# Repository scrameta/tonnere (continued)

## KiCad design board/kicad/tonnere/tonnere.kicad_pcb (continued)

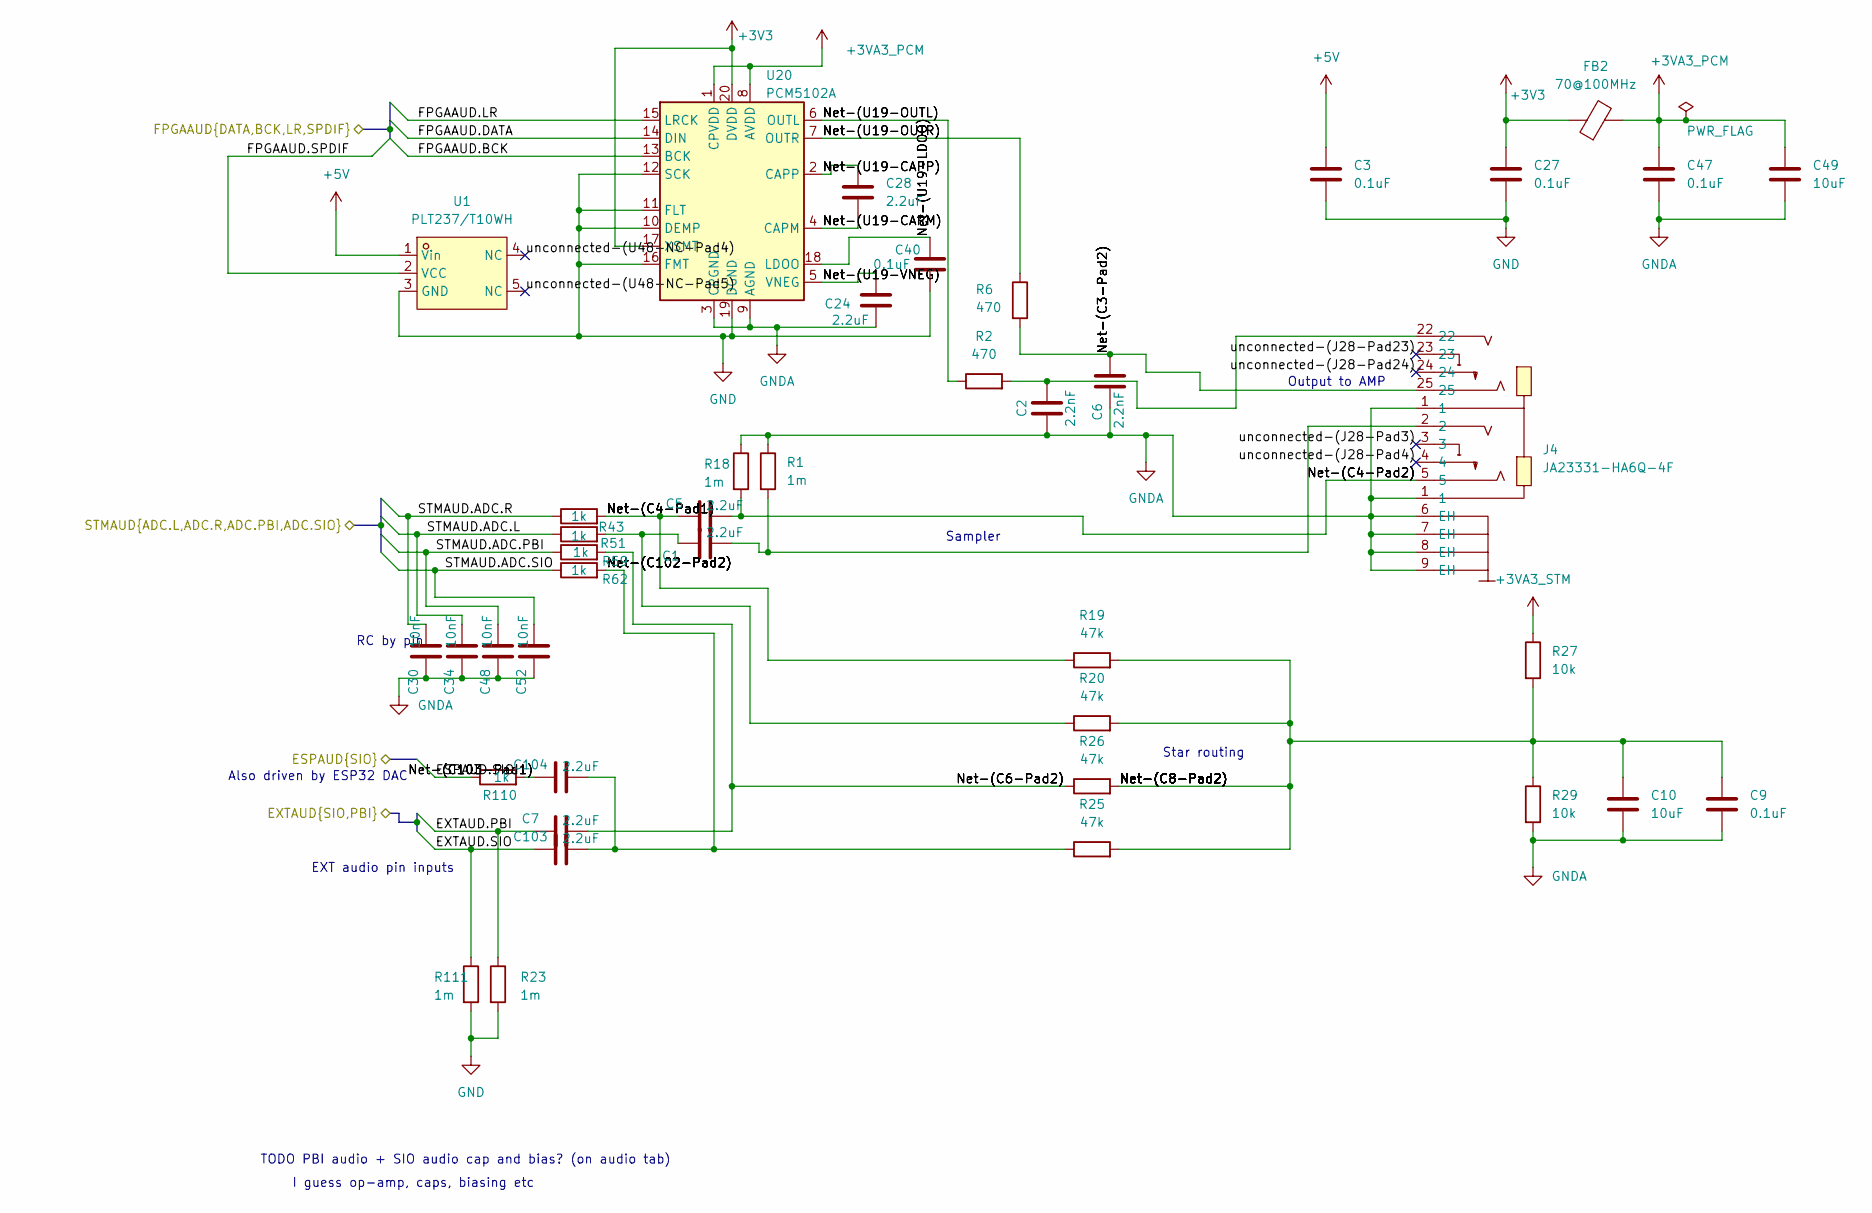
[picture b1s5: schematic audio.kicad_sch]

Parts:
C1, C5, C7, C24, C28, C103, C104: 2.2uF; C_0603_1608Metric; LCSC C23630
C2, C6: 2.2nF; C_0603_1608Metric; LCSC C1604
C3, C9, C27, C40, C47: 0.1uF; C_0603_1608Metric; LCSC C14663
C10, C49: 10uF; C_0805_2012Metric; LCSC C15850
C30, C34, C48, C52: 10nF; C_0603_1608Metric; LCSC C57112
FB2: 70@100MHz; L_0805_2012Metric; LCSC C1012
J4: JA23331-HA6Q-4F; AUDIO-TH_JA23331-HA6Q-4F; MPN JA23331-HA6Q-4F; LCSC Part C225739
R1, R18, R23, R111: 1m; R_0603_1608Metric; LCSC C22935
R2, R6: 470; R_0603_1608Metric; LCSC C23179
R19, R20, R25, R26: 47k; R_0603_1608Metric; LCSC C25819
R27, R29: 10k; R_0603_1608Metric; LCSC C25804
R43, R51, R59, R62, R110: 1k; R_0603_1608Metric; LCSC C21190
U1: PLT237/T10WH; CONN-TH_PLT237-T10WH; MPN PLT237/T10WH; LCSC Part C17296340
U20: PCM5102A; TSSOP-20_4.4x6.5mm_P0.65mm; LCSC C107671

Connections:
+3V3: C27.2, FB2.1, U20.17 (XSMT), U20.20 (DVDD); also elsewhere on the board
+3VA3_PCM: C47.2, C49.1, FB2.2, U20.1 (CPVDD), U20.8 (AVDD)
+3VA3_STM: R27.1; also elsewhere on the board
+5V: C3.2, U1.1 (Vin); also elsewhere on the board
/AtariInterfaces/EXTAUD.PBI: C7.1, R23.1; also elsewhere on the board
/AtariInterfaces/EXTAUD.SIO: C103.1, R111.1; also elsewhere on the board
/Audio/ESPAUD.SIO: R110.1; also elsewhere on the board
/Audio/FPGAAUD.BCK: U20.13 (BCK); also elsewhere on the board
/Audio/FPGAAUD.DATA: U20.14 (DIN); also elsewhere on the board
/Audio/FPGAAUD.LR: U20.15 (LRCK); also elsewhere on the board
/Audio/FPGAAUD.SPDIF: U1.2 (VCC); also elsewhere on the board
/Audio/Net-(C3-Pad2): C6.2, J4.25, R6.2
/Audio/Net-(C4-Pad1): C5.1, R19.1, R43.2
/Audio/Net-(C4-Pad2): C5.2, J4.5, R18.2
/Audio/Net-(C6-Pad2): C7.2, R26.1, R59.2
/Audio/Net-(C8-Pad2): C9.2, C10.2, R19.2, R20.2, R25.2, R26.2, R27.2, R29.1
/Audio/Net-(C102-Pad2): C103.2, C104.2, R25.1, R62.2
/Audio/Net-(C103-Pad1): C104.1, R110.2
/Audio/Net-(U19-CAPM): C28.1, U20.4 (CAPM)
/Audio/Net-(U19-CAPP): C28.2, U20.2 (CAPP)
/Audio/Net-(U19-LDOO): C40.2, U20.18 (LDOO)
/Audio/Net-(U19-OUTL): R2.1, U20.6 (OUTL)
/Audio/Net-(U19-OUTR): R6.1, U20.7 (OUTR)
/Audio/Net-(U19-VNEG): C24.2, U20.5 (VNEG)
/Audio/STMAUD.ADC.L: C34.2, R51.1; also elsewhere on the board
/Audio/STMAUD.ADC.PBI: C48.2, R59.1; also elsewhere on the board
/Audio/STMAUD.ADC.R: C30.2, R43.1; also elsewhere on the board
/Audio/STMAUD.ADC.SIO: C52.2, R62.1; also elsewhere on the board
/Audio/unconnected-(J28-Pad3): J4.3
/Audio/unconnected-(J28-Pad4): J4.4
/Audio/unconnected-(J28-Pad23): J4.23
/Audio/unconnected-(J28-Pad24): J4.24
/Audio/unconnected-(U48-NC-Pad4): U1.4 (NC)
/Audio/unconnected-(U48-NC-Pad5): U1.5 (NC)
GND: C3.1, C27.1, C40.1, R23.2, R111.2, U1.3 (GND), U20.10 (DEMP), U20.11 (FLT), U20.12 (SCK), U20.16 (FMT), U20.19 (DGND); also elsewhere on the board
GNDA: C2.1, C6.1, C9.1, C10.1, C24.1, C30.1, C34.1, C47.1, C48.1, C49.2, C52.1, J4.1, J4.6 (EH), J4.7 (EH), J4.8 (EH), J4.9 (EH), R1.1, R18.1, R29.2, U20.3 (CPGND), U20.9 (AGND); also elsewhere on the board
unnamed: C1.1, R20.1, R51.2
unnamed: C1.2, J4.2, R1.2
unnamed: C2.2, J4.22, R2.2

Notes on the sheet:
EXT audio pin inputs
Also driven by ESP32 DAC
RC by pin
TODO PBI audio + SIO audio cap and bias? (on audio tab)
I guess op-amp, caps, biasing etc
Output to AMP
Star routing
Sampler

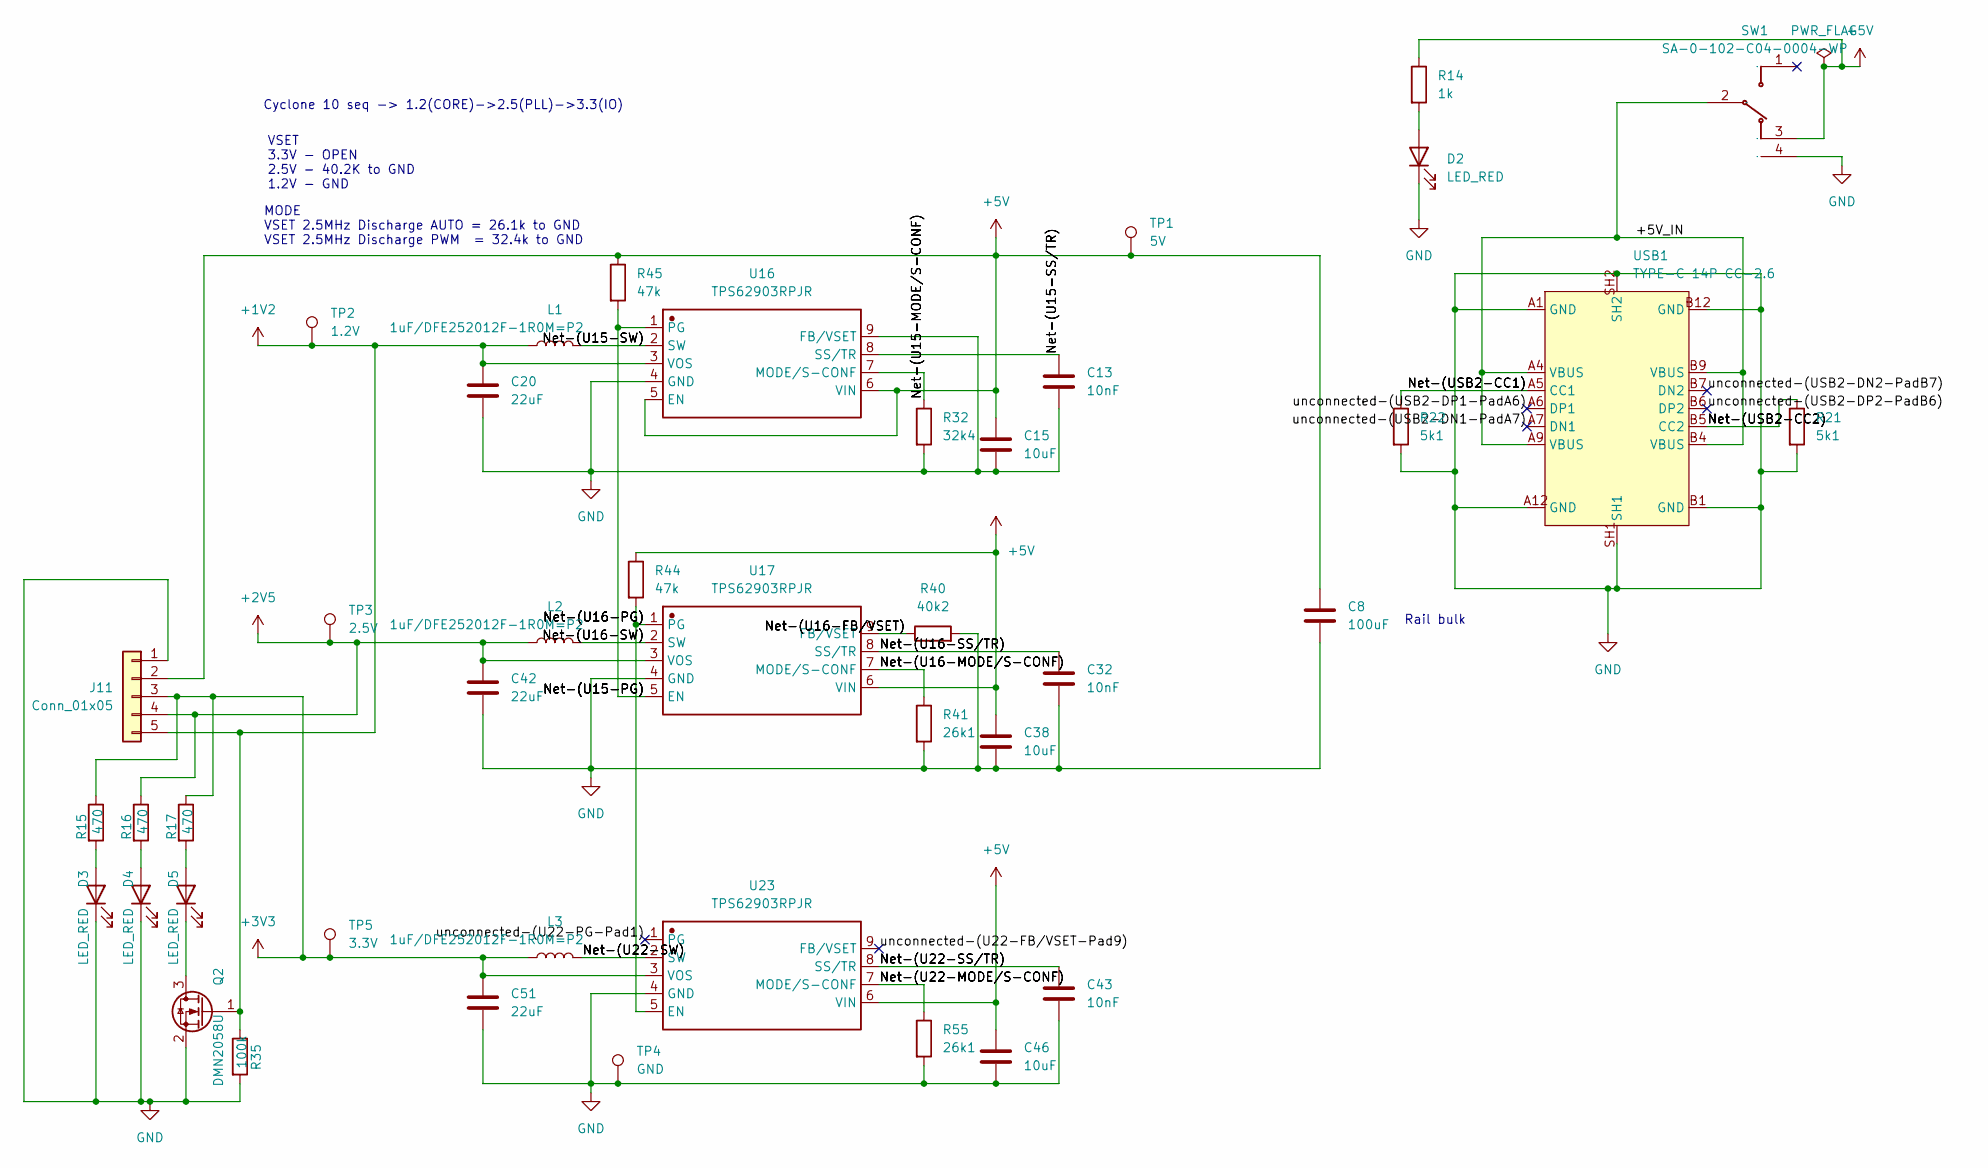
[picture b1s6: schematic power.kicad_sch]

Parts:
C8: 100uF; C_1206_3216Metric; LCSC C883598
C13, C32, C43: 10nF; C_0603_1608Metric; LCSC C57112
C15, C38, C46: 10uF; C_0805_2012Metric; LCSC C15850
C20, C42, C51: 22uF; C_0805_2012Metric; LCSC C45783
D2, D3, D4, D5: LED_RED; LED_0805_2012Metric; LCSC C84256
J11: Conn_01x05; PinHeader_1x05_P2.54mm_Vertical; LCSC C225480
L1, L2, L3: 1uF/DFE252012F-1R0M=P2; L_1008_2520Metric; LCSC C435392
Q2: DMN2058U; SOT-23; LCSC C461001
R14: 1k; R_0603_1608Metric; LCSC C21190
R15, R16, R17: 470; R_0603_1608Metric; LCSC C23179
R21, R22: 5k1; R_0603_1608Metric; LCSC C23186
R32: 32k4; R_0603_1608Metric; LCSC C2998122
R35: 100k; R_0603_1608Metric; LCSC C25803
R40: 40k2; R_0603_1608Metric; LCSC C2933218
R41, R55: 26k1; R_0603_1608Metric; LCSC C49196678
R44, R45: 47k; R_0603_1608Metric; LCSC C25819
SW1: SA-0-102-C04-0004-WP; SW-TH_SA-0-102-C04-0004-WP; Manufacturer Part SA-0-102-C04-0004-WP; JLC_3DModel 1b2c176f3639467abbcc028bfae2d8b5
TP1: 5V; TestPoint_Plated_Hole_D2.0mm
TP2: 1.2V; TestPoint_Plated_Hole_D2.0mm
TP3: 2.5V; TestPoint_Plated_Hole_D2.0mm
TP4: GND; TestPoint_Plated_Hole_D2.0mm
TP5: 3.3V; TestPoint_Plated_Hole_D2.0mm
U16, U17, U23: TPS62903RPJR; VQFN-HR-9_L2.0-W1.5-P0.50-TL; Manufacturer Part TPS62903RPJR; LCSC C2866502
USB1: TYPE-C 14P CC-2.6; TYPE-C-TH_TYPE-C-14P-CC-2.6; MPN TYPE-C 14P CC-2.6; LCSC Part C5187475

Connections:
+1V2: C20.1, J11.5, L1.1, Q2.1 (G), R35.1, TP2.1 (1_1), U16.3 (VOS); also elsewhere on the board
+2V5: C42.1, J11.4, L2.1, R16.1, TP3.1 (1_1), U17.3 (VOS); also elsewhere on the board
+3V3: C51.1, J11.3, L3.1, R15.1, R17.1, TP5.1 (1_1), U23.3 (VOS); also elsewhere on the board
+5V: C8.1, C15.1, C38.1, C46.1, J11.2, R14.1, R44.1, R45.1, SW1.3, TP1.1 (1_1), U16.5 (EN), U16.6 (VIN), U17.6 (VIN), U23.6 (VIN); also elsewhere on the board
/Power/+5V_IN: SW1.2, USB1.A4 (VBUS), USB1.A9 (VBUS), USB1.B4 (VBUS), USB1.B9 (VBUS)
/Power/Net-(U15-MODE/S-CONF): R32.1, U16.7 (MODE/S-CONF)
/Power/Net-(U15-PG): R45.2, U16.1 (PG), U17.5 (EN)
/Power/Net-(U15-SS/TR): C13.1, U16.8 (SS/TR)
/Power/Net-(U15-SW): L1.2, U16.2 (SW)
/Power/Net-(U16-FB/VSET): R40.1, U17.9 (FB/VSET)
/Power/Net-(U16-MODE/S-CONF): R41.1, U17.7 (MODE/S-CONF)
/Power/Net-(U16-PG): R44.2, U17.1 (PG), U23.5 (EN)
/Power/Net-(U16-SS/TR): C32.1, U17.8 (SS/TR)
/Power/Net-(U16-SW): L2.2, U17.2 (SW)
/Power/Net-(U22-MODE/S-CONF): R55.1, U23.7 (MODE/S-CONF)
/Power/Net-(U22-SS/TR): C43.1, U23.8 (SS/TR)
/Power/Net-(U22-SW): L3.2, U23.2 (SW)
/Power/Net-(USB2-CC1): R22.1, USB1.A5 (CC1)
/Power/Net-(USB2-CC2): R21.1, USB1.B5 (CC2)
/Power/unconnected-(U22-FB/VSET-Pad9): U23.9 (FB/VSET)
/Power/unconnected-(U22-PG-Pad1): U23.1 (PG)
/Power/unconnected-(USB2-DN1-PadA7): USB1.A7 (DN1)
/Power/unconnected-(USB2-DN2-PadB7): USB1.B7 (DN2)
/Power/unconnected-(USB2-DP1-PadA6): USB1.A6 (DP1)
/Power/unconnected-(USB2-DP2-PadB6): USB1.B6 (DP2)
GND: C8.2, C13.2, C15.2, C20.2, C32.2, C38.2, C42.2, C43.2, C46.2, C51.2, D2.1 (K), D3.1 (K), D4.1 (K), J11.1, Q2.2 (S), R21.2, R22.2, R32.2, R35.2, R40.2, R41.2, R55.2, SW1.4, TP4.1 (1_1), U16.4 (GND), U16.9 (FB/VSET), U17.4 (GND), U23.4 (GND), USB1.A1 (GND), USB1.A12 (GND), USB1.B1 (GND), USB1.B12 (GND), USB1.SH1, USB1.SH2; also elsewhere on the board
unnamed: D2.2 (A), R14.2
unnamed: D3.2 (A), R15.2
unnamed: D4.2 (A), R16.2
unnamed: D5.2 (A), R17.2
unnamed: D5.1 (K), Q2.3 (D)

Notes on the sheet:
VSET 3.3V - OPEN 2.5V - 40.2K to GND 1.2V - GND
Rail bulk
MODE VSET 2.5MHz Discharge AUTO = 26.1k to GND VSET 2.5MHz Discharge PWM = 32.4k to GND
Cyclone 10 seq -> 1.2(CORE)->2.5(PLL)->3.3(IO)

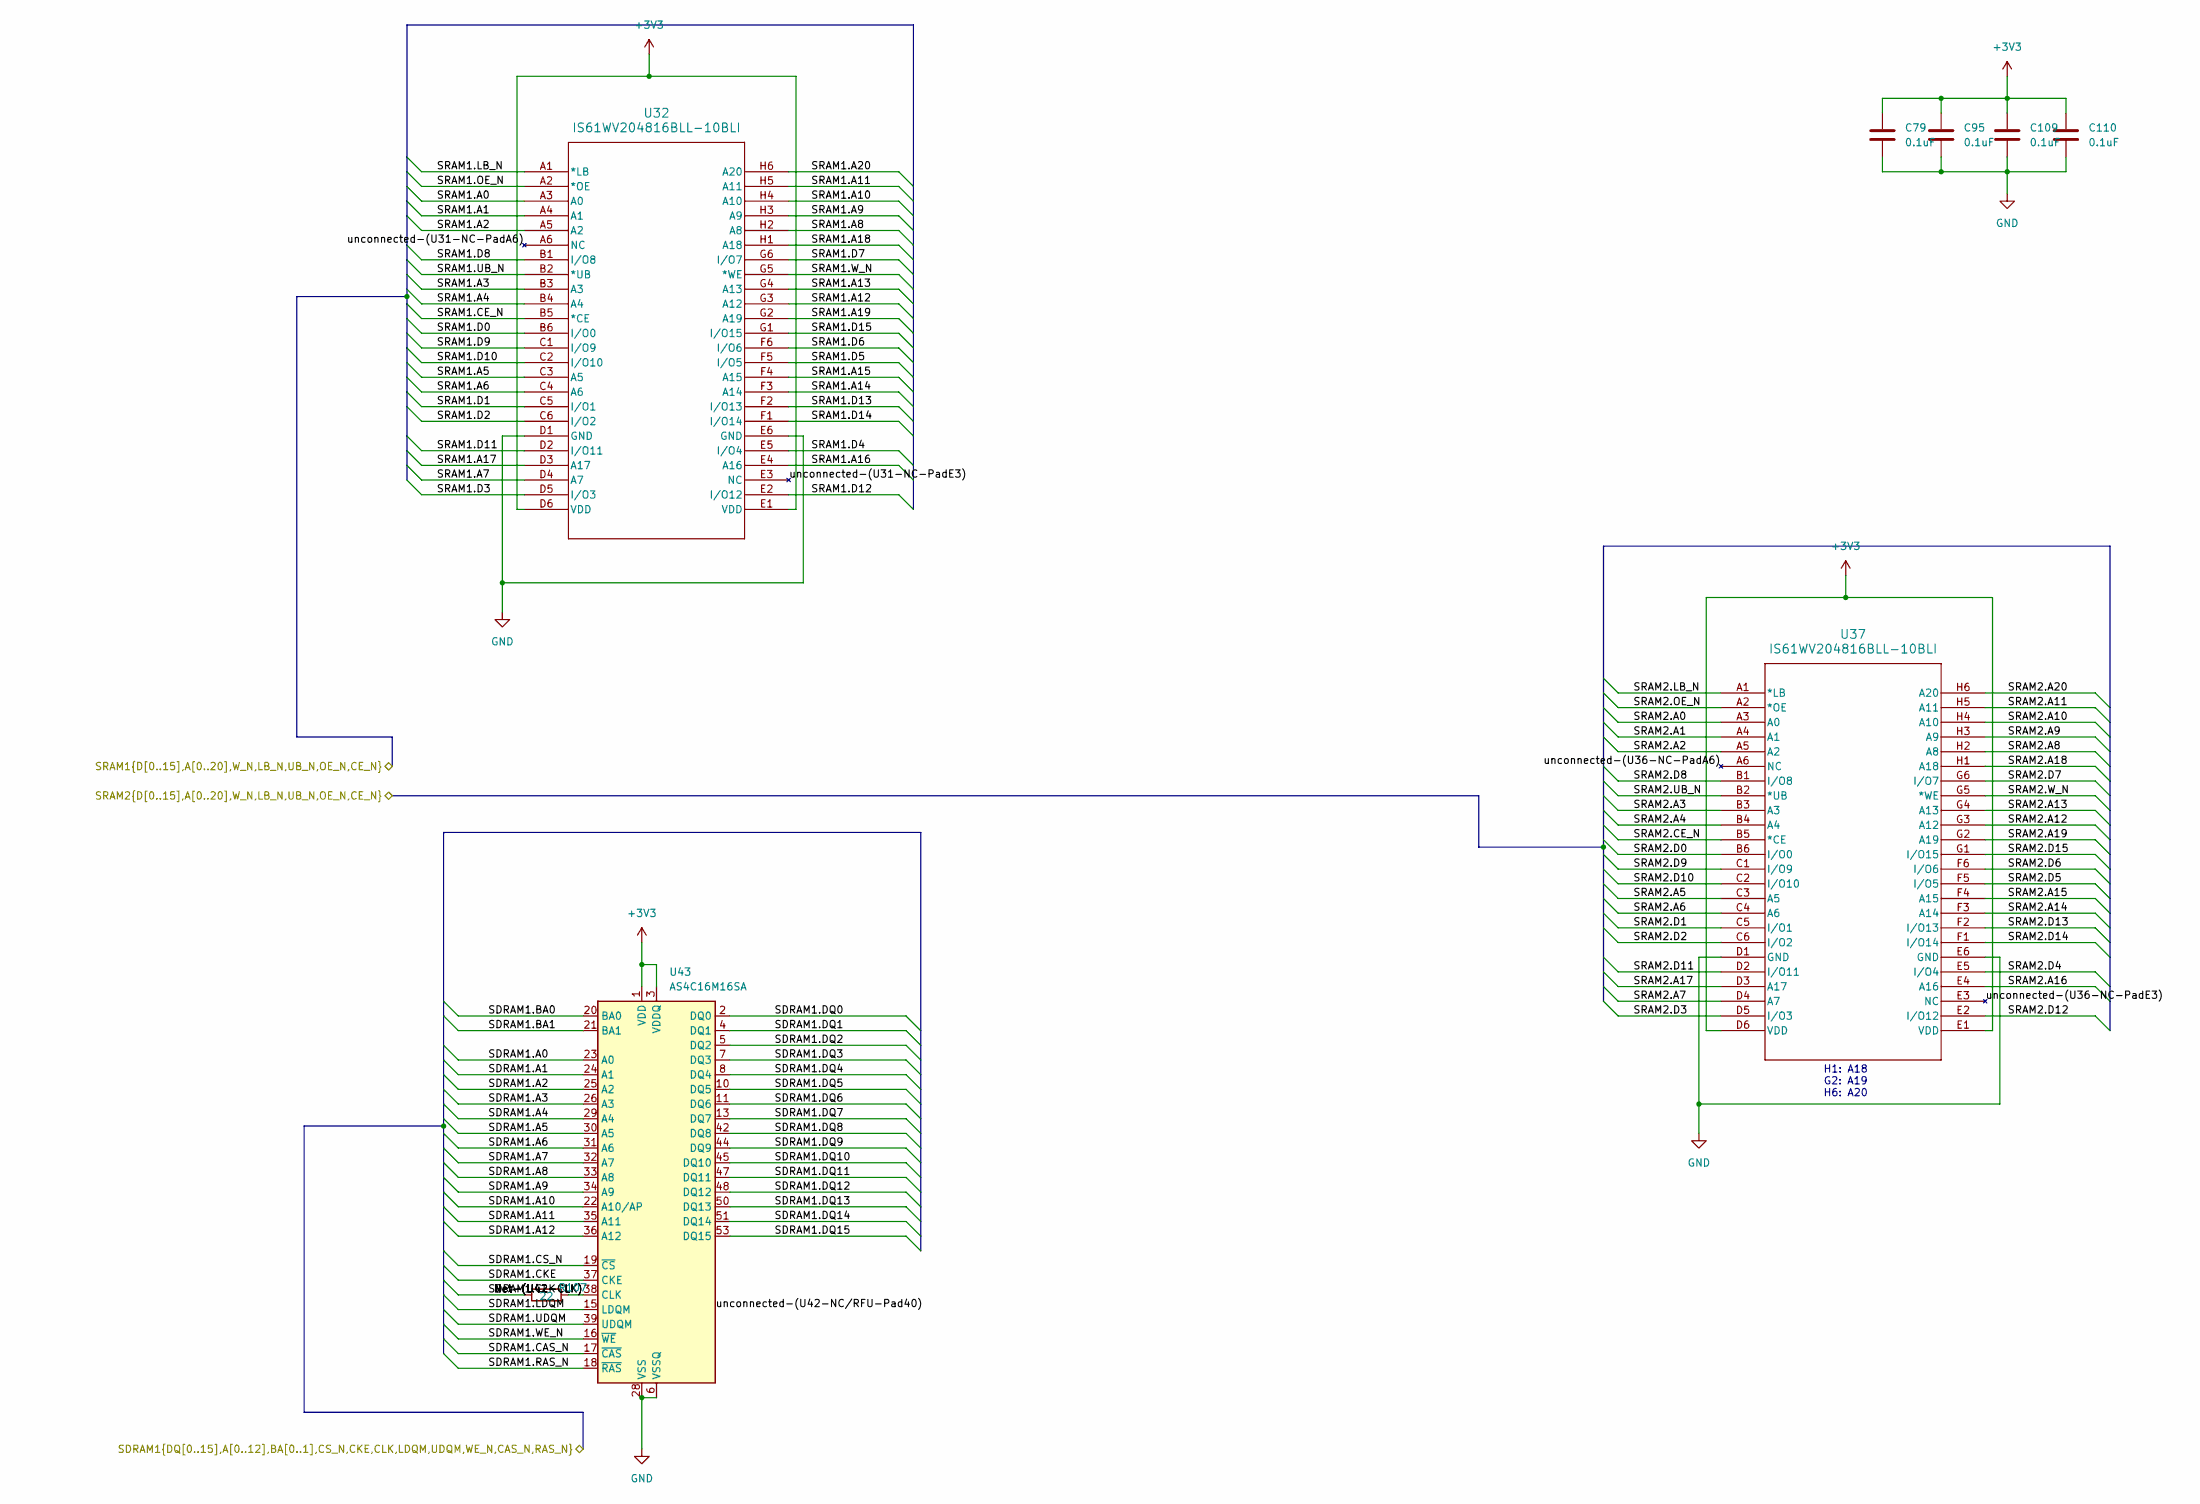
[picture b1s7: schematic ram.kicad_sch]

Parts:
C79, C95, C109, C110: 0.1uF; C_0603_1608Metric; LCSC C14663
R107: 22; R_0603_1608Metric; LCSC C23345
U32: IS61WV204816BLL-10BLI; TF-BGA-48L_ISI; LCSC C1349085
U37: IS61WV204816BLL-10BLI; TF-BGA-48L_ISI; LCSC C1348743
U43: AS4C16M16SA; TSOP-II-54_22.2x10.16mm_P0.8mm; LCSC C62246

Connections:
+3V3: C79.1, C95.1, C109.1, C110.1, U32.D6 (VDD), U32.E1 (VDD), U37.D6 (VDD), U37.E1 (VDD), U43.1 (VDD), U43.3 (VDDQ), U43.9 (VDDQ), U43.14 (VDD), U43.27 (VDD), U43.43 (VDDQ), U43.49 (VDDQ); also elsewhere on the board
/FPGA/SDRAM1.A0: U43.23 (A0); also elsewhere on the board
/FPGA/SDRAM1.A1: U43.24 (A1); also elsewhere on the board
/FPGA/SDRAM1.A2: U43.25 (A2); also elsewhere on the board
/FPGA/SDRAM1.A3: U43.26 (A3); also elsewhere on the board
/FPGA/SDRAM1.A4: U43.29 (A4); also elsewhere on the board
/FPGA/SDRAM1.A5: U43.30 (A5); also elsewhere on the board
/FPGA/SDRAM1.A6: U43.31 (A6); also elsewhere on the board
/FPGA/SDRAM1.A7: U43.32 (A7); also elsewhere on the board
/FPGA/SDRAM1.A8: U43.33 (A8); also elsewhere on the board
/FPGA/SDRAM1.A9: U43.34 (A9); also elsewhere on the board
/FPGA/SDRAM1.A10: U43.22 (A10/AP); also elsewhere on the board
/FPGA/SDRAM1.A11: U43.35 (A11); also elsewhere on the board
/FPGA/SDRAM1.A12: U43.36 (A12); also elsewhere on the board
/FPGA/SDRAM1.BA0: U43.20 (BA0); also elsewhere on the board
/FPGA/SDRAM1.BA1: U43.21 (BA1); also elsewhere on the board
/FPGA/SDRAM1.CAS_N: U43.17 (~CAS); also elsewhere on the board
/FPGA/SDRAM1.CKE: U43.37 (CKE); also elsewhere on the board
/FPGA/SDRAM1.CLK: R107.1; also elsewhere on the board
/FPGA/SDRAM1.CS_N: U43.19 (~CS); also elsewhere on the board
/FPGA/SDRAM1.DQ0: U43.2 (DQ0); also elsewhere on the board
/FPGA/SDRAM1.DQ1: U43.4 (DQ1); also elsewhere on the board
/FPGA/SDRAM1.DQ2: U43.5 (DQ2); also elsewhere on the board
/FPGA/SDRAM1.DQ3: U43.7 (DQ3); also elsewhere on the board
/FPGA/SDRAM1.DQ4: U43.8 (DQ4); also elsewhere on the board
/FPGA/SDRAM1.DQ5: U43.10 (DQ5); also elsewhere on the board
/FPGA/SDRAM1.DQ6: U43.11 (DQ6); also elsewhere on the board
/FPGA/SDRAM1.DQ7: U43.13 (DQ7); also elsewhere on the board
/FPGA/SDRAM1.DQ8: U43.42 (DQ8); also elsewhere on the board
/FPGA/SDRAM1.DQ9: U43.44 (DQ9); also elsewhere on the board
/FPGA/SDRAM1.DQ10: U43.45 (DQ10); also elsewhere on the board
/FPGA/SDRAM1.DQ11: U43.47 (DQ11); also elsewhere on the board
/FPGA/SDRAM1.DQ12: U43.48 (DQ12); also elsewhere on the board
/FPGA/SDRAM1.DQ13: U43.50 (DQ13); also elsewhere on the board
/FPGA/SDRAM1.DQ14: U43.51 (DQ14); also elsewhere on the board
/FPGA/SDRAM1.DQ15: U43.53 (DQ15); also elsewhere on the board
/FPGA/SDRAM1.LDQM: U43.15 (LDQM); also elsewhere on the board
/FPGA/SDRAM1.RAS_N: U43.18 (~RAS); also elsewhere on the board
/FPGA/SDRAM1.UDQM: U43.39 (UDQM); also elsewhere on the board
/FPGA/SDRAM1.WE_N: U43.16 (~WE); also elsewhere on the board
/FPGA/SRAM1.A0: U32.A3 (A0); also elsewhere on the board
/FPGA/SRAM1.A1: U32.A4 (A1); also elsewhere on the board
/FPGA/SRAM1.A2: U32.A5 (A2); also elsewhere on the board
/FPGA/SRAM1.A3: U32.B3 (A3); also elsewhere on the board
/FPGA/SRAM1.A4: U32.B4 (A4); also elsewhere on the board
/FPGA/SRAM1.A5: U32.C3 (A5); also elsewhere on the board
/FPGA/SRAM1.A6: U32.C4 (A6); also elsewhere on the board
/FPGA/SRAM1.A7: U32.D4 (A7); also elsewhere on the board
/FPGA/SRAM1.A8: U32.H2 (A8); also elsewhere on the board
/FPGA/SRAM1.A9: U32.H3 (A9); also elsewhere on the board
/FPGA/SRAM1.A10: U32.H4 (A10); also elsewhere on the board
/FPGA/SRAM1.A11: U32.H5 (A11); also elsewhere on the board
/FPGA/SRAM1.A12: U32.G3 (A12); also elsewhere on the board
/FPGA/SRAM1.A13: U32.G4 (A13); also elsewhere on the board
/FPGA/SRAM1.A14: U32.F3 (A14); also elsewhere on the board
/FPGA/SRAM1.A15: U32.F4 (A15); also elsewhere on the board
/FPGA/SRAM1.A16: U32.E4 (A16); also elsewhere on the board
/FPGA/SRAM1.A17: U32.D3 (A17); also elsewhere on the board
/FPGA/SRAM1.A18: U32.H1 (A18); also elsewhere on the board
/FPGA/SRAM1.A19: U32.G2 (A19); also elsewhere on the board
/FPGA/SRAM1.A20: U32.H6 (A20); also elsewhere on the board
/FPGA/SRAM1.CE_N: U32.B5 (*CE); also elsewhere on the board
/FPGA/SRAM1.D0: U32.B6 (I/O0); also elsewhere on the board
/FPGA/SRAM1.D1: U32.C5 (I/O1); also elsewhere on the board
/FPGA/SRAM1.D2: U32.C6 (I/O2); also elsewhere on the board
/FPGA/SRAM1.D3: U32.D5 (I/O3); also elsewhere on the board
/FPGA/SRAM1.D4: U32.E5 (I/O4); also elsewhere on the board
/FPGA/SRAM1.D5: U32.F5 (I/O5); also elsewhere on the board
/FPGA/SRAM1.D6: U32.F6 (I/O6); also elsewhere on the board
/FPGA/SRAM1.D7: U32.G6 (I/O7); also elsewhere on the board
/FPGA/SRAM1.D8: U32.B1 (I/O8); also elsewhere on the board
/FPGA/SRAM1.D9: U32.C1 (I/O9); also elsewhere on the board
/FPGA/SRAM1.D10: U32.C2 (I/O10); also elsewhere on the board
/FPGA/SRAM1.D11: U32.D2 (I/O11); also elsewhere on the board
/FPGA/SRAM1.D12: U32.E2 (I/O12); also elsewhere on the board
/FPGA/SRAM1.D13: U32.F2 (I/O13); also elsewhere on the board
/FPGA/SRAM1.D14: U32.F1 (I/O14); also elsewhere on the board
/FPGA/SRAM1.D15: U32.G1 (I/O15); also elsewhere on the board
/FPGA/SRAM1.LB_N: U32.A1 (*LB); also elsewhere on the board
/FPGA/SRAM1.OE_N: U32.A2 (*OE); also elsewhere on the board
/FPGA/SRAM1.UB_N: U32.B2 (*UB); also elsewhere on the board
/FPGA/SRAM1.W_N: U32.G5 (*WE); also elsewhere on the board
/FPGA/SRAM2.A0: U37.A3 (A0); also elsewhere on the board
/FPGA/SRAM2.A1: U37.A4 (A1); also elsewhere on the board
/FPGA/SRAM2.A2: U37.A5 (A2); also elsewhere on the board
/FPGA/SRAM2.A3: U37.B3 (A3); also elsewhere on the board
/FPGA/SRAM2.A4: U37.B4 (A4); also elsewhere on the board
/FPGA/SRAM2.A5: U37.C3 (A5); also elsewhere on the board
/FPGA/SRAM2.A6: U37.C4 (A6); also elsewhere on the board
/FPGA/SRAM2.A7: U37.D4 (A7); also elsewhere on the board
/FPGA/SRAM2.A8: U37.H2 (A8); also elsewhere on the board
/FPGA/SRAM2.A9: U37.H3 (A9); also elsewhere on the board
/FPGA/SRAM2.A10: U37.H4 (A10); also elsewhere on the board
/FPGA/SRAM2.A11: U37.H5 (A11); also elsewhere on the board
/FPGA/SRAM2.A12: U37.G3 (A12); also elsewhere on the board
/FPGA/SRAM2.A13: U37.G4 (A13); also elsewhere on the board
/FPGA/SRAM2.A14: U37.F3 (A14); also elsewhere on the board
/FPGA/SRAM2.A15: U37.F4 (A15); also elsewhere on the board
/FPGA/SRAM2.A16: U37.E4 (A16); also elsewhere on the board
/FPGA/SRAM2.A17: U37.D3 (A17); also elsewhere on the board
/FPGA/SRAM2.A18: U37.H1 (A18); also elsewhere on the board
/FPGA/SRAM2.A19: U37.G2 (A19); also elsewhere on the board
/FPGA/SRAM2.A20: U37.H6 (A20); also elsewhere on the board
/FPGA/SRAM2.CE_N: U37.B5 (*CE); also elsewhere on the board
/FPGA/SRAM2.D0: U37.B6 (I/O0); also elsewhere on the board
/FPGA/SRAM2.D1: U37.C5 (I/O1); also elsewhere on the board
/FPGA/SRAM2.D2: U37.C6 (I/O2); also elsewhere on the board
/FPGA/SRAM2.D3: U37.D5 (I/O3); also elsewhere on the board
/FPGA/SRAM2.D4: U37.E5 (I/O4); also elsewhere on the board
/FPGA/SRAM2.D5: U37.F5 (I/O5); also elsewhere on the board
/FPGA/SRAM2.D6: U37.F6 (I/O6); also elsewhere on the board
/FPGA/SRAM2.D7: U37.G6 (I/O7); also elsewhere on the board
/FPGA/SRAM2.D8: U37.B1 (I/O8); also elsewhere on the board
/FPGA/SRAM2.D9: U37.C1 (I/O9); also elsewhere on the board
/FPGA/SRAM2.D10: U37.C2 (I/O10); also elsewhere on the board
/FPGA/SRAM2.D11: U37.D2 (I/O11); also elsewhere on the board
/FPGA/SRAM2.D12: U37.E2 (I/O12); also elsewhere on the board
/FPGA/SRAM2.D13: U37.F2 (I/O13); also elsewhere on the board
/FPGA/SRAM2.D14: U37.F1 (I/O14); also elsewhere on the board
/FPGA/SRAM2.D15: U37.G1 (I/O15); also elsewhere on the board
/FPGA/SRAM2.LB_N: U37.A1 (*LB); also elsewhere on the board
/FPGA/SRAM2.OE_N: U37.A2 (*OE); also elsewhere on the board
/FPGA/SRAM2.UB_N: U37.B2 (*UB); also elsewhere on the board
/FPGA/SRAM2.W_N: U37.G5 (*WE); also elsewhere on the board
/RAM/Net-(U42-CLK): R107.2, U43.38 (CLK)
GND: C79.2, C95.2, C109.2, C110.2, U32.D1 (GND), U32.E6 (GND), U37.D1 (GND), U37.E6 (GND), U43.6 (VSSQ), U43.12 (VSSQ), U43.28 (VSS), U43.41 (VSS), U43.46 (VSSQ), U43.52 (VSSQ), U43.54 (VSS); also elsewhere on the board

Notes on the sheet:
H1: A18 G2: A19 H6: A20
